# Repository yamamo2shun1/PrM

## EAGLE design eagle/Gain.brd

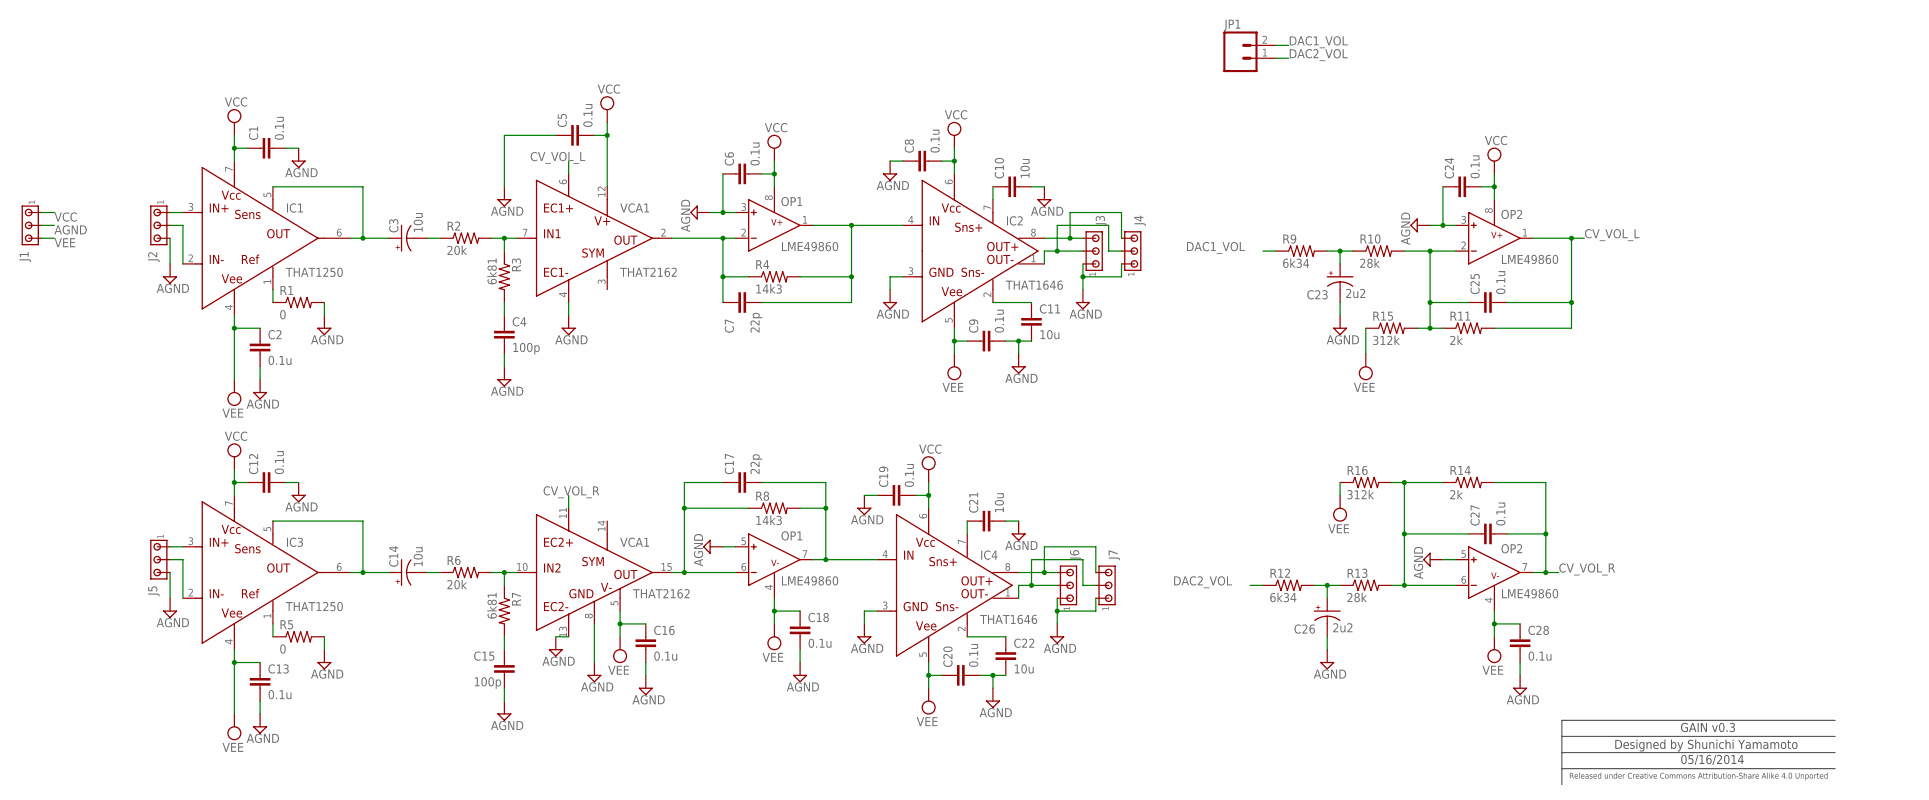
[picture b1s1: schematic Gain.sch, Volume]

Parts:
C1, C2, C5, C6, C8, C9, C12, C13, C16, C18, C19, C20, C24, C25, C27, C28: 0.1u; C2012
C3, C14: 10u; UD-5X5,8_NICHICON
C4, C15: 100p; C2012
C7, C17: 22p; C2012
C10, C11, C21, C22: 10u; C2012
C23, C26: 2u2; UD-5X5,8_NICHICON
IC1, IC3: THAT1250; SOIC8
IC2, IC4: THAT1646; SOIC8
J1: MTA03-156; 1X3MTA
J2, J3, J4, J5, J6, J7: MTA03-100; 10X03MTA
JP1: M02PTH; 1X02
OP1, OP2: LME49860; SOIC8@1
R1, R5: 0; 0805
R2, R6: 20k; 0805
R3, R7: 6k81; 0805
R4, R8: 14k3; 0805
R9, R12: 6k34; 0805
R10, R13: 28k; 0805
R11, R14: 2k; 0805
R15, R16: 312k; 0805
VCA1: THAT2162; QSOP-16

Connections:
AGND: C1.2, C2.2, C4.2, C5.1, C6.1, C8.1, C9.2, C10.2, C11.2, C12.2, C13.2, C15.2, C16.2, C18.2, C19.1, C20.2, C21.2, C22.2, C23.-, C24.1, C26.-, C28.2, IC2.3 (GND), IC4.3 (GND), J1.2, J2.3, J3.1, J4.1, J5.3, J6.1, J7.1, OP1.3 (INA+), OP1.5 (INB+), OP2.3 (INA+), OP2.5 (INB+), R1.2, R5.2, VCA1.4 (EC1-), VCA1.8 (GND), VCA1.13 (EC2-)
C8: C14.-, R6.1
CV_VOL_L: C25.2, OP2.1 (OUTA), R11.2, VCA1.6 (EC1+)
CV_VOL_R: C27.2, OP2.7 (OUTB), R14.2, VCA1.11 (EC2+)
DAC1_VOL: JP1.2, R9.1
DAC2_VOL: JP1.1, R12.1
unnamed: IC1.1 (REF), R1.1
unnamed: C10.1, IC2.7 (SNS+)
unnamed: IC1.3 (IN+), J2.1
unnamed: IC1.2 (IN-), J2.2
unnamed: IC3.1 (REF), R5.1
unnamed: IC3.3 (IN+), J5.1
unnamed: IC3.2 (IN-), J5.2
unnamed: IC2.8 (OUT+), J3.3, J4.3
unnamed: IC2.1 (OUT-), J3.2, J4.2
unnamed: IC4.8 (OUT+), J6.3, J7.3
unnamed: IC4.1 (OUT-), J6.2, J7.2
unnamed: R2.2, R3.1, VCA1.7 (IN1)
unnamed: C11.1, IC2.2 (SNS-)
unnamed: C21.1, IC4.7 (SNS+)
unnamed: C22.1, IC4.2 (SNS-)
unnamed: C3.-, R2.1
unnamed: R6.2, R7.1, VCA1.10 (IN2)
unnamed: C7.1, OP1.2 (INA-), R4.1, VCA1.2 (OUT1)
unnamed: C4.1, R3.2
unnamed: C15.1, R7.2
unnamed: C23.+, R9.2, R10.1
unnamed: C25.1, OP2.2 (INA-), R10.2, R11.1, R15.2
unnamed: C26.+, R12.2, R13.1
unnamed: C27.1, OP2.6 (INB-), R13.2, R14.1, R16.2
unnamed: C17.1, OP1.6 (INB-), R8.1, VCA1.15 (OUT2)
OUT_L: C7.2, IC2.4 (IN), OP1.1 (OUTA), R4.2
OUT_R: C17.2, IC4.4 (IN), OP1.7 (OUTB), R8.2
PIN_L: C3.+, IC1.5 (SENS), IC1.6 (OUT)
PIN_R: C14.+, IC3.5 (SENS), IC3.6 (OUT)
VCC: C1.1, C5.2, C6.2, C8.2, C12.1, C19.2, C24.2, IC1.7 (VCC), IC2.6 (VCC), IC3.7 (VCC), IC4.6 (VCC), J1.1, OP1.8 (V+), OP2.8 (V+), VCA1.12 (V+)
VEE: C2.1, C9.1, C13.1, C16.1, C18.1, C20.1, C28.1, IC1.4 (VEE), IC2.5 (VEE), IC3.4 (VEE), IC4.5 (VEE), J1.3, OP1.4 (V-), OP2.4 (V-), R15.1, R16.1, VCA1.5 (V-)

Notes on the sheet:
GAIN v0.3
Designed by Shunichi Yamamoto
05/16/2014
Released under Creative Commons Attribution-Share Alike 4.0 Unported

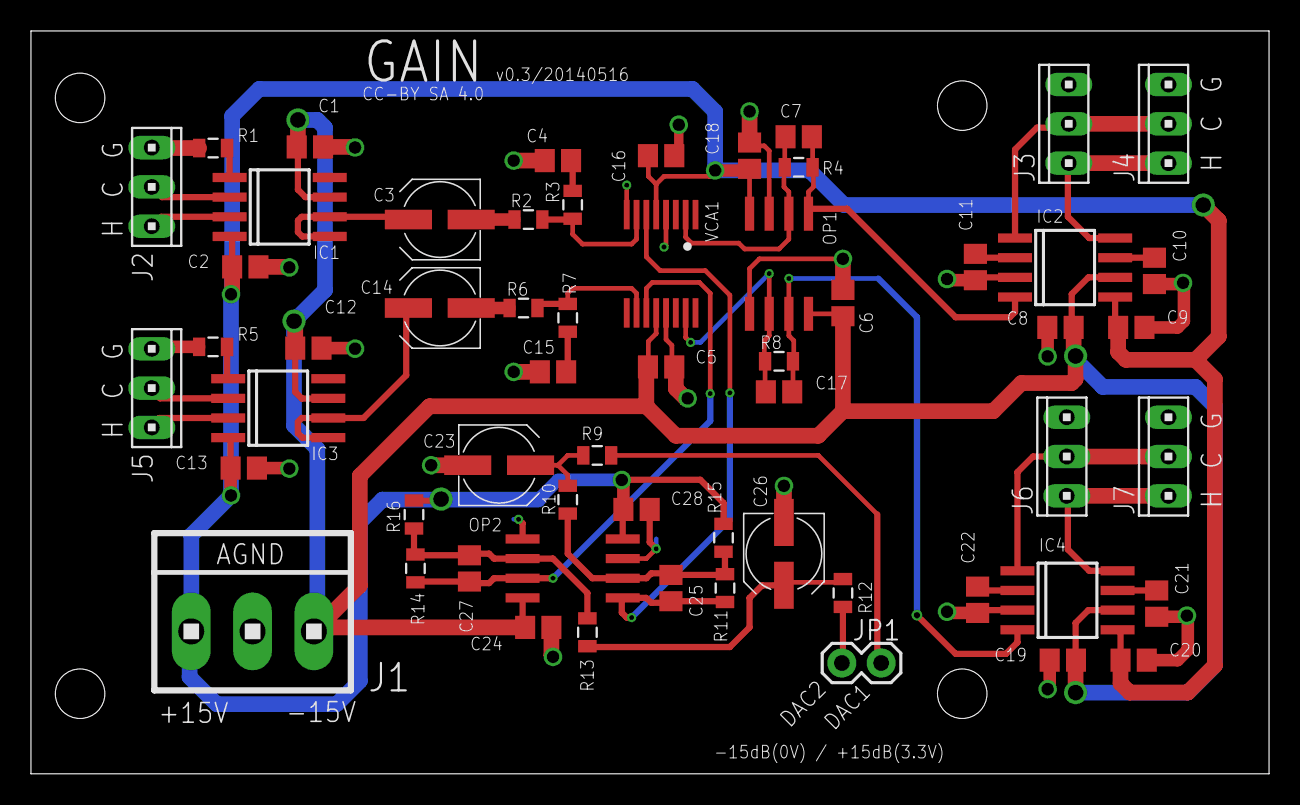
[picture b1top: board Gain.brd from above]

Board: 2 copper layers, 80.0 x 48.0 mm, 59 parts (0 on the bottom side), 37 nets.

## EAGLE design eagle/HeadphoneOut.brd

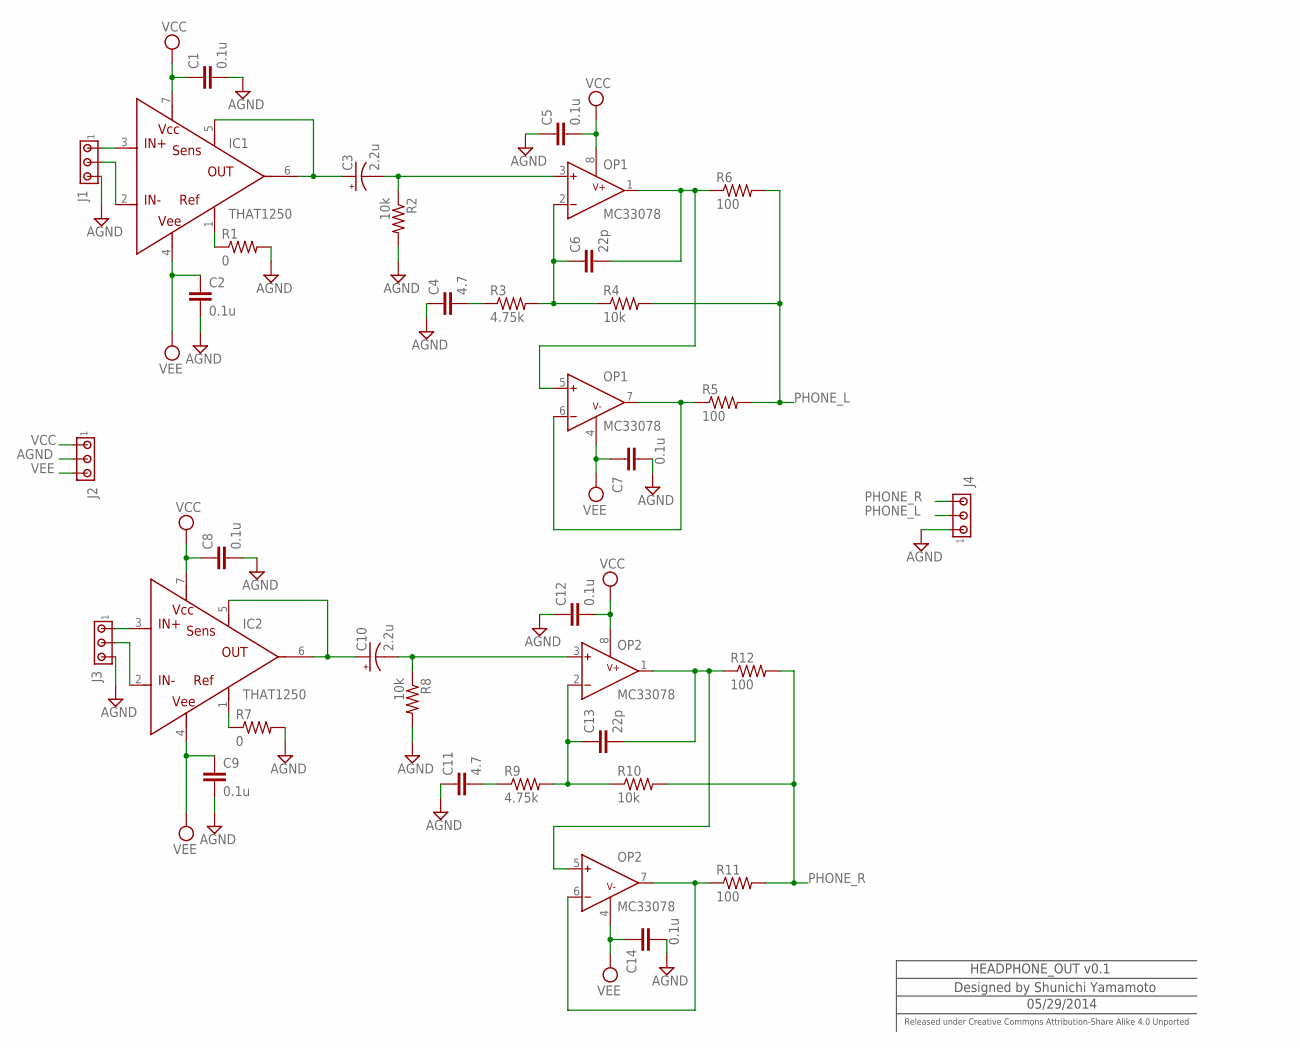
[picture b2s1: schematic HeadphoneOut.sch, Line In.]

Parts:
C1, C2, C5, C7, C8, C9, C12, C14: 0.1u; C2012
C3, C10: 2.2u; UD-5X5,8_NICHICON
C4, C11: 4.7; C2012
C6, C13: 22p; C2012
IC1, IC2: THAT1250; SOIC8
J1, J3, J4: MTA03-100; 10X03MTA
J2: MTA03-156; 1X3MTA
OP1, OP2: MC33078; SOIC8@1
R1, R7: 0; 0805
R2, R4, R8, R10: 10k; 0805
R3, R9: 4.75k; 0805
R5, R6, R11, R12: 100; 0805

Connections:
AGND: C1.2, C2.2, C4.1, C5.1, C7.2, C8.2, C9.2, C11.1, C12.1, C14.2, J1.3, J2.2, J3.3, J4.1, R1.2, R2.2, R7.2, R8.2
unnamed: C6.1, OP1.2 (INA-), R3.2, R4.1
unnamed: C6.2, OP1.1 (OUTA), OP1.5 (INB+), R6.1
unnamed: OP1.6 (INB-), OP1.7 (OUTB), R5.1
unnamed: IC1.1 (REF), R1.1
unnamed: C3.-, OP1.3 (INA+), R2.1
unnamed: C4.2, R3.1
unnamed: C13.1, OP2.2 (INA-), R9.2, R10.1
unnamed: C13.2, OP2.1 (OUTA), OP2.5 (INB+), R12.1
unnamed: OP2.6 (INB-), OP2.7 (OUTB), R11.1
unnamed: IC1.3 (IN+), J1.1
unnamed: C10.-, OP2.3 (INA+), R8.1
unnamed: C11.2, R9.1
unnamed: IC1.2 (IN-), J1.2
unnamed: IC2.1 (REF), R7.1
unnamed: IC2.3 (IN+), J3.1
unnamed: IC2.2 (IN-), J3.2
PHONE_L: J4.2, R4.2, R5.2, R6.2
PHONE_R: J4.3, R10.2, R11.2, R12.2
PIN_L: C3.+, IC1.5 (SENS), IC1.6 (OUT)
PIN_R: C10.+, IC2.5 (SENS), IC2.6 (OUT)
VCC: C1.1, C5.2, C8.1, C12.2, IC1.7 (VCC), IC2.7 (VCC), J2.1, OP1.8 (V+), OP2.8 (V+)
VEE: C2.1, C7.1, C9.1, C14.1, IC1.4 (VEE), IC2.4 (VEE), J2.3, OP1.4 (V-), OP2.4 (V-)

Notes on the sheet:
HEADPHONE_OUT v0.1
Designed by Shunichi Yamamoto
05/29/2014
Released under Creative Commons Attribution-Share Alike 4.0 Unported

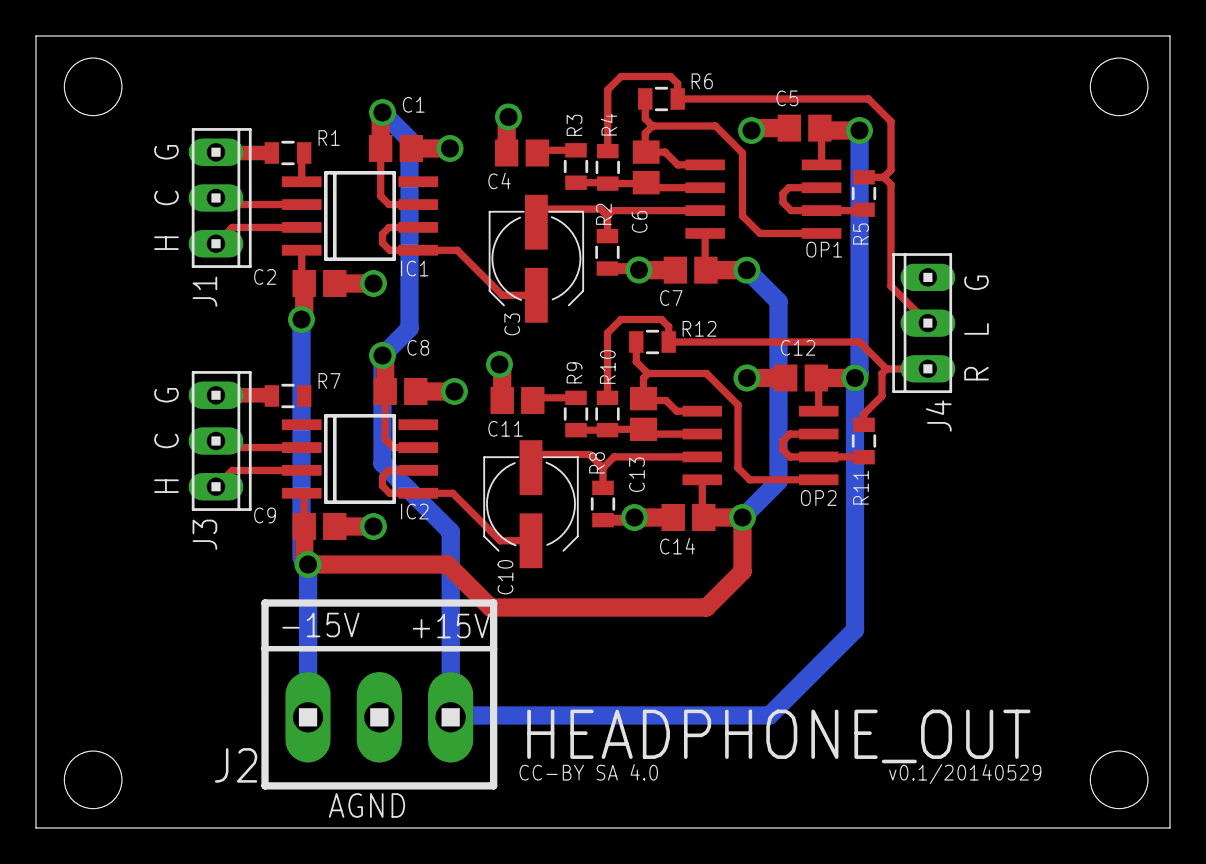
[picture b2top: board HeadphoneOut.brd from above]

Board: 2 copper layers, 63.0 x 44.0 mm, 34 parts (0 on the bottom side), 23 nets.

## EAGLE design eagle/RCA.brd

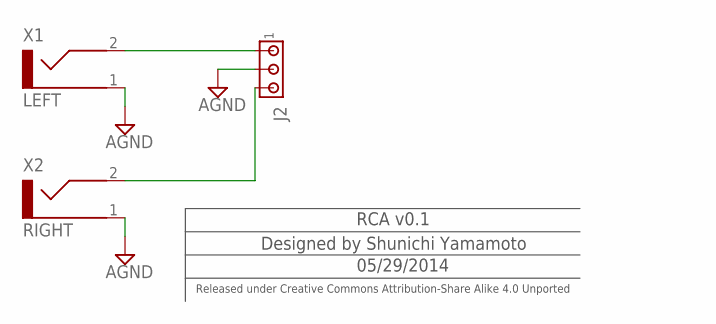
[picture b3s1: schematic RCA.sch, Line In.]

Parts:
J2: MTA03-100; 10X03MTA
X1: LEFT; RCA_JACK_CUI
X2: RIGHT; RCA_JACK_CUI

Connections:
AGND: J2.2, X1.1, X2.1
unnamed: J2.1, X1.2
unnamed: J2.3, X2.2

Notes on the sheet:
RCA v0.1
Designed by Shunichi Yamamoto
05/29/2014
Released under Creative Commons Attribution-Share Alike 4.0 Unported

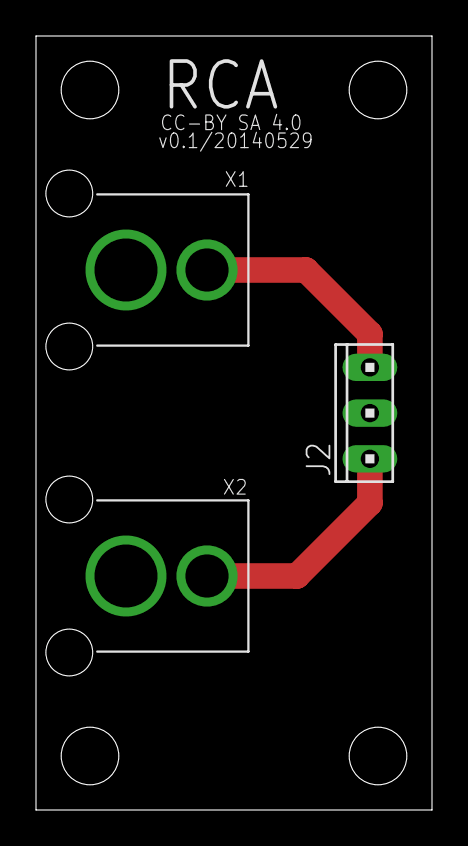
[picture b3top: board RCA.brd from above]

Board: 2 copper layers, 22.0 x 43.0 mm, 3 parts (0 on the bottom side), 3 nets.

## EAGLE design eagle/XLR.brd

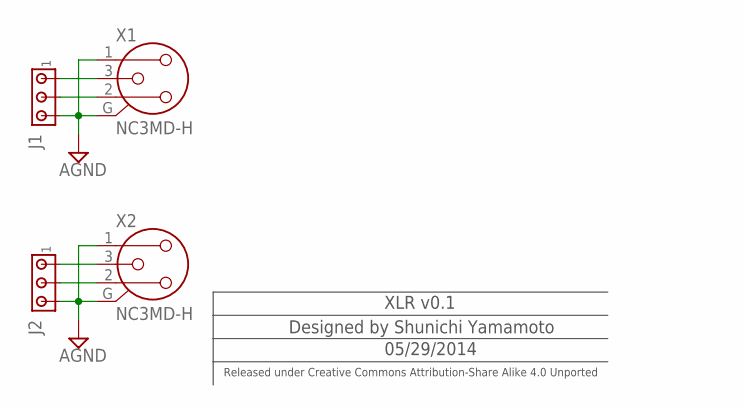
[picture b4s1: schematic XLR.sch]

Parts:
J1, J2: MTA03-100; 10X03MTA
X1, X2: NC3MD-H

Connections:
AGND: J1.3, J2.3, X1.1, X1.G, X2.1, X2.G
unnamed: J1.1, X1.3
unnamed: J1.2, X1.2
unnamed: J2.1, X2.3
unnamed: J2.2, X2.2

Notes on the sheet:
XLR v0.1
Designed by Shunichi Yamamoto
05/29/2014
Released under Creative Commons Attribution-Share Alike 4.0 Unported

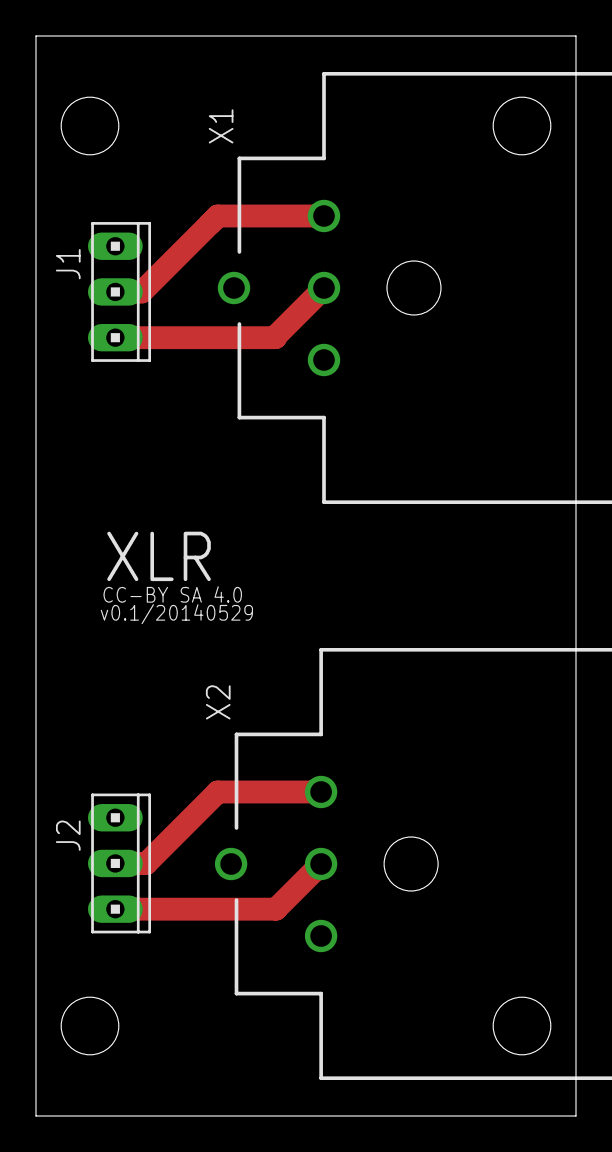
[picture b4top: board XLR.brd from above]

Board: 2 copper layers, 30.0 x 60.0 mm, 4 parts (0 on the bottom side), 5 nets.

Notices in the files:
eagle/Gain.brd:
CC-BY SA 4.0
parts and their libraries:
SparkFun: Licensing: CC v3.0 Share-Alike You are welcome to use this library for commercial purposes.
